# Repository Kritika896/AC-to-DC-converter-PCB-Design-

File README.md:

#  12V AC to DC Converter – KiCad Project

##  Project Description

This project involves the design and PCB layout of a **12V AC to DC Converter** using **KiCad**, a powerful open-source PCB design tool. The goal is to convert a 12V AC input into a smoothed DC voltage output suitable for powering basic electronic circuits.

The converter circuit uses a **full-wave bridge rectifier** made with four 1N4007 diodes, followed by a **filtering stage** using a 1000μF capacitor to smooth the rectified voltage. An LED indicator is added to show power availability, along with supporting resistors for safety and functionality.

The entire circuit was **schematically designed**, **footprints assigned**, and a **PCB layout created** in KiCad. The design includes proper spacing, track width, and component alignment, along with a 3D preview to visualize the final product. This board is suitable for hobby projects, prototyping, and can be a base module in many embedded systems requiring DC power.

---

## 🛠 Tools Used

- **KiCad** for schematic capture, PCB design, and 3D visualization

---

##  Project Images

### Schematic Diagram

### PCB Layout (2D)

### 3D View of PCB

---

##  Step-by-Step Process in KiCad

### 1. **Schematic Design**
- Open **KiCad Eeschema** and create the circuit.
- Used components:
  - **4x Diodes (1N4007)** for full bridge rectification
  - **1x Capacitor (1000µF)** for filtering
  - **2x Resistors (10kΩ and 2.2kΩ)** for biasing and current limiting
  - **1x LED** for power indication
  - **2x Screw Terminals (J2, J3)** for AC input and DC output

### 2. **Assign Footprints**
- Used the **Symbol to Footprint Assignment Tool**.
- Ensured all components had appropriate THT (Through Hole Technology) footprints.

### 3. **PCB Layout**
- Launched **PCB Editor**.
- Placed components compactly and logically.
- Routed tracks manually with 0.5mm width.
- Maintained clearances and avoided track overlap.
- Added labels like "AC in", "DC out", and "KiCad".

### 4. **3D Visualization**
- Used KiCad’s **3D Viewer** to verify design before fabrication.
- Ensured component orientation and silkscreen alignment.

### 5. **Final Checks**
- Verified DRC (Design Rule Check) passed.
- Ensured no unconnected nets.
- Exported Gerber files if ready for manufacturing.

---

##  Component Footprints Used

| Symbol | Value   | Footprint |
|--------|---------|-----------|
| C1     | 1000uF  | Capacitor_THT:C_Radial_D8.0mm_H11.5mm_P3.50mm |
| D1-D4  | 1N4007  | Diode_THT:D_DO-41_SOD81_P10.16mm_Horizontal   |
| D5     | LED     | LED_THT:LED_D5.0mm                            |
| J2/J3  | Terminal Block | TerminalBlock_bornier-2_P5.08mm         |
| R1     | 10k     | Resistor_THT:R_Axial_DIN0204_P7.62mm         |
| R2     | 2.2k    | Resistor_THT:R_Axial_DIN0204_P7.62mm         |

---

##  Output

- Input: 12V AC (via J3)
- Output: Smoothed DC ~10-12V (via J2, after rectification and filtering)

---

##  Project Files

- `Schematic.kicad_sch`
- `PCB.kicad_pcb`
- `Footprints.pretty/`
- `3D_Model.step`
- `Gerber/` (optional if fabrication planned)

---

##  Applications

- Basic electronics power supply
- Embedded systems requiring DC input
- Educational and learning purposes

---

##  Notes

- Make sure to test your output with a multimeter before connecting to other electronics.
- You can upgrade the circuit with a voltage regulator (e.g., 7805) if a specific regulated voltage is needed.

---

##  Author

**Kritika Sinha**  
B.Tech – Cyber Physical Systems  

---

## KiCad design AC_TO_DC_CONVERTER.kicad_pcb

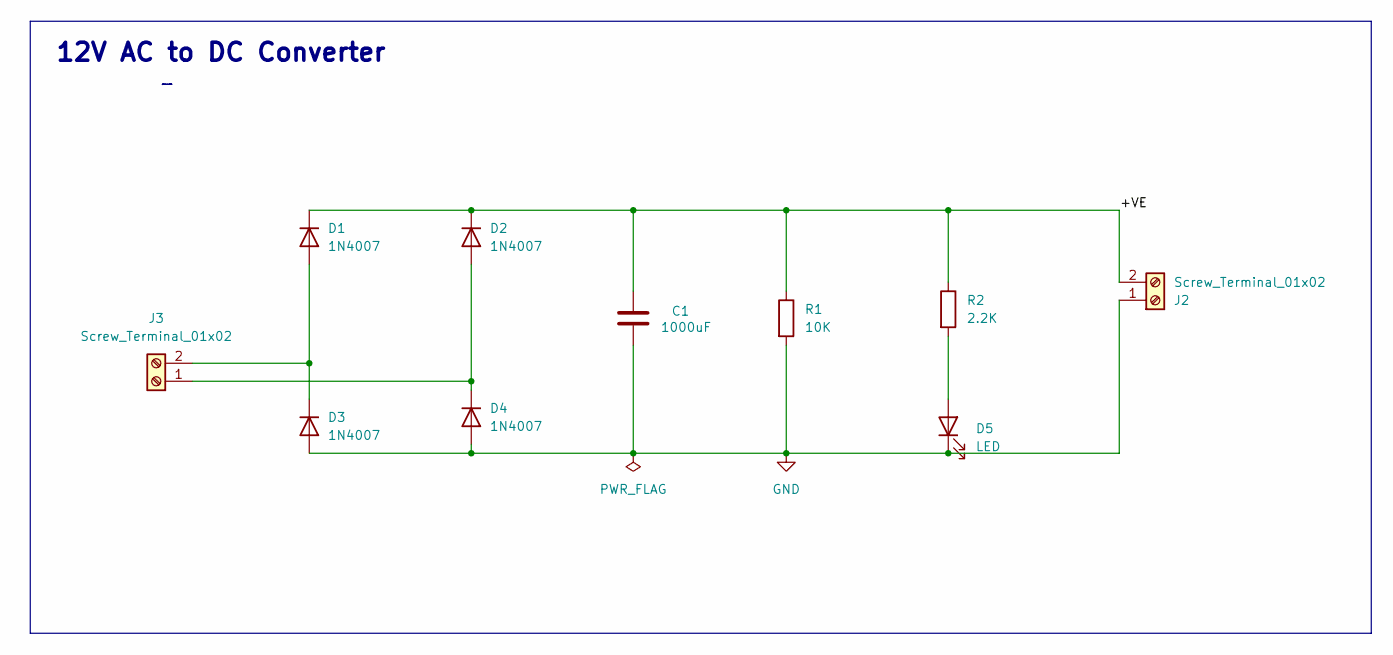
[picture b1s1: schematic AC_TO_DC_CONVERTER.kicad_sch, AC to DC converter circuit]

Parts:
C1: 1000uF; C_Radial_D8.0mm_H11.5mm_P3.50mm
D1, D2, D3, D4: 1N4007; D_DO-41_SOD81_P10.16mm_Horizontal
D5: LED; LED_D5.0mm
J2, J3: Screw_Terminal_01x02; TerminalBlock_bornier-2_P5.08mm
R1: 10K; R_Axial_DIN0204_L3.6mm_D1.6mm_P7.62mm_Horizontal
R2: 2.2K; R_Axial_DIN0204_L3.6mm_D1.6mm_P7.62mm_Horizontal

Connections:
/+VE: C1.1, D1.1 (K), D2.1 (K), J2.2, R1.1, R2.1
GND: C1.2, D3.2 (A), D4.2 (A), D5.1 (K), J2.1, R1.2
unnamed: D1.2 (A), D3.1 (K), J3.2
unnamed: D2.2 (A), D4.1 (K), J3.1
unnamed: D5.2 (A), R2.2

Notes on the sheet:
12V AC to DC converter
12V AC to DC Converter

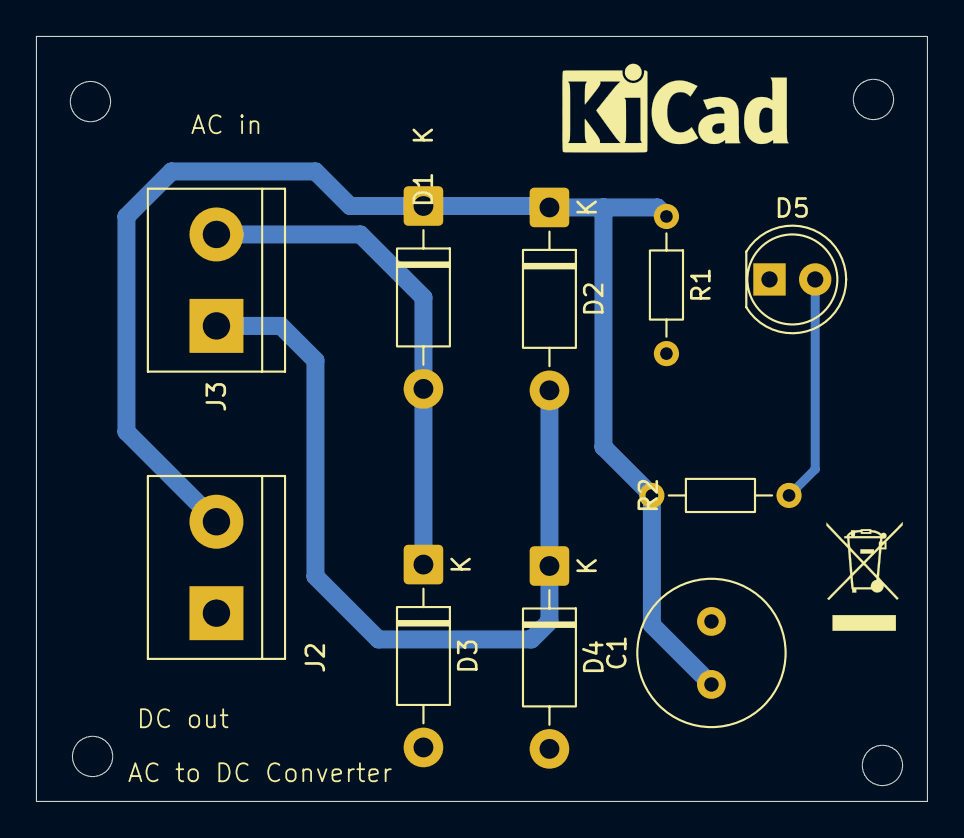
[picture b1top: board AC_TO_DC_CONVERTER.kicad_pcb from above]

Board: 2 copper layers, 49.5 x 42.5 mm, 10 parts (0 on the bottom side), 5 nets.
